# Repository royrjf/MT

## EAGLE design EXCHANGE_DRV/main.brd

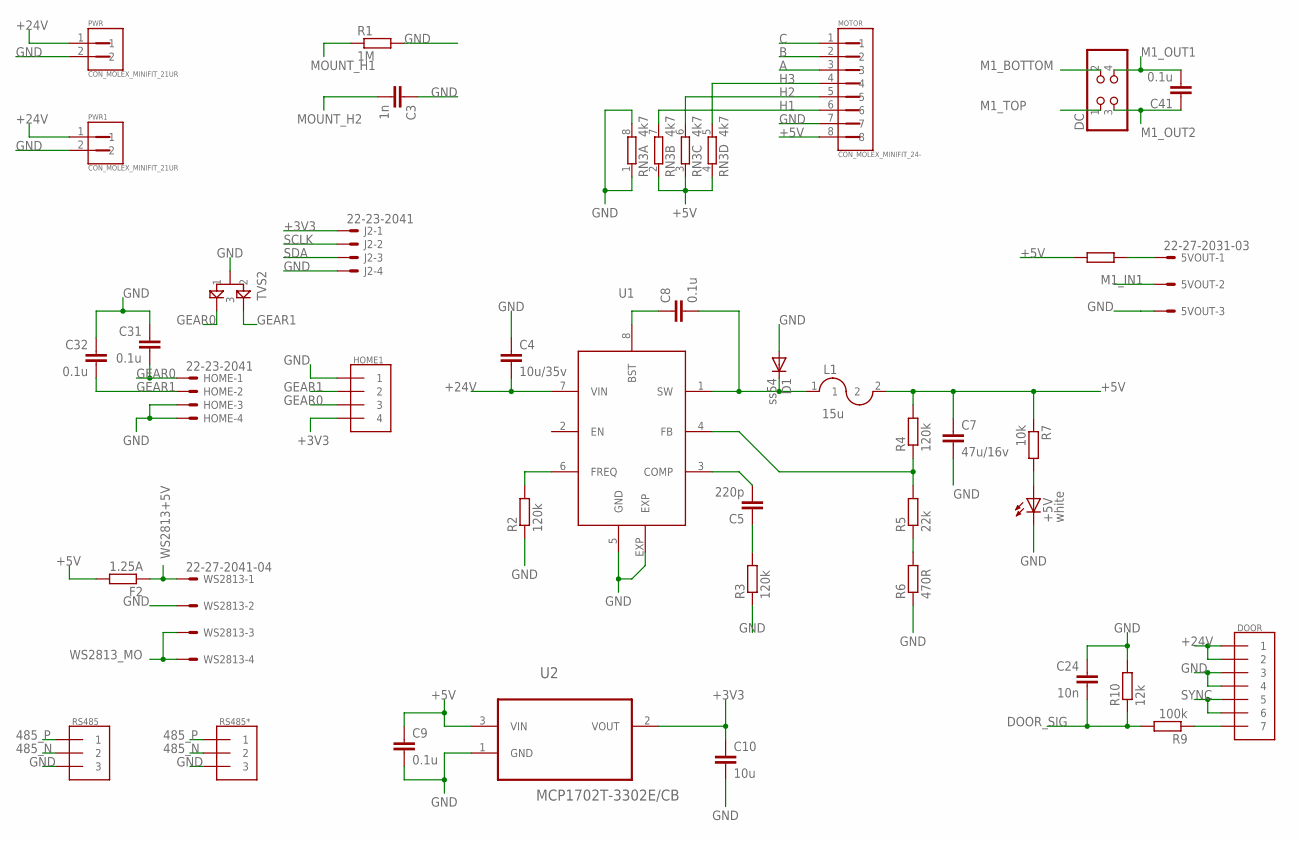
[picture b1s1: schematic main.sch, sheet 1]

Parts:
5VOUT: 22-27-2031-03; 6410-03
+5V: white; SML0603
C3: 1n; C0603
C4: 10u/35v; C1206
C5: 220p; C0603
C7: 47u/16v; C1206
C8, C9, C31, C32, C41: 0.1u; C0603
C10: 10u; C0603
C24: 10n; C0603
D1: ss54; DO214BA
DC: 430450414; 4304504-TH
DOOR: 1LINE_SOCKET_2MM_7
F1, F2: 1.25A; R1206
HOME: 22-23-2041
HOME1: 1LINE_SOCKET_2MM_4_90
J2: 22-23-2041
L1: 15u; RCL_L_CDRH8D38
MOTOR: CON_MOLEX_MINIFIT_24-; CON_MOLEX_MINIFIT_2*4
PWR, PWR1: CON_MOLEX_MINIFIT_21UR; CON_MOLEX_MINIFIT_2*1_UR
R1: 1M; R0603
R2, R3, R4: 120k; R0603
R5: 22k; R0603
R6: 470R; R0603
R7: 10k; R0603
R9: 100k; R0603
R10: 12k; R0603
RN3: 4k7; EXB38V
RS485, RS485*: 1LINE_SOCKET_2MM_3_90
TVS2: PESD33; RCL_SOT23
U1: MP2560; SOIC-8E
U2: MCP1702T-3302E/CB; SOT95P255X145-3N
WS2813: 22-27-2041-04; 6410-04

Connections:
485_N: RS485.P$2 (2), RS485*.P$2 (2); also elsewhere on the board
485_P: RS485.P$1 (1), RS485*.P$1 (1); also elsewhere on the board
+3V3: C10.1, HOME1.P$4 (4), J2.1, U2.2 (VOUT); also elsewhere on the board
+5V: C7.1, C9.1, F1.2, F2.2, L1.2, MOTOR.8, R4.2, R7.1, RN3.2 (1), RN3.3 (1), RN3.4 (1), U2.3 (VIN)
+24V: C4.2, DOOR.P$1 (1), DOOR.P$2 (2), PWR.1, PWR1.1, U1.7 (VIN); also elsewhere on the board
A: MOTOR.3; also elsewhere on the board
B: MOTOR.2; also elsewhere on the board
C: MOTOR.1; also elsewhere on the board
DOOR_SIG: C24.2, R9.2, R10.1; also elsewhere on the board
GEAR0: C31.2, HOME.1, HOME1.P$3 (3), TVS2.1; also elsewhere on the board
GEAR1: C32.2, HOME.2, HOME1.P$2 (2), TVS2.2; also elsewhere on the board
GND: 5VOUT.3, +5V.C, C3.1, C4.1, C7.2, C9.2, C10.2, C24.1, C31.1, C32.1, D1.A, DOOR.P$3 (3), DOOR.P$4 (4), HOME.3, HOME.4, HOME1.P$1 (1), J2.4, MOTOR.7, PWR.2, PWR1.2, R1.2, R2.1, R3.1, R6.1, R10.2, RN3.1, RN3.8 (2), RS485.P$3 (3), RS485*.P$3 (3), TVS2.3, U1.5 (GND), U1.EXP, U2.1 (GND), WS2813.2; also elsewhere on the board
H1: MOTOR.6, RN3.7 (2); also elsewhere on the board
H2: MOTOR.5, RN3.6 (2); also elsewhere on the board
H3: MOTOR.4, RN3.5 (2); also elsewhere on the board
M1_BOTTOM: DC.2
M1_IN1: 5VOUT.2; also elsewhere on the board
M1_OUT1: C41.2, DC.4; also elsewhere on the board
M1_OUT2: C41.1, DC.3; also elsewhere on the board
M1_TOP: DC.1
MOUNT_H1: R1.1
MOUNT_H2: C3.2
unnamed: C8.2, D1.C, L1.1, U1.1 (SW)
unnamed: 5VOUT.1, F1.1
unnamed: C5.1, R3.2
unnamed: R2.2, U1.6 (FREQ)
unnamed: C5.2, U1.3 (COMP)
unnamed: R5.1, R6.2
unnamed: R4.1, R5.2, U1.4 (FB)
unnamed: C8.1, U1.8 (BST)
unnamed: +5V.A, R7.2
SCLK: J2.2; also elsewhere on the board
SDA: J2.3; also elsewhere on the board
SIG-DOOR: DOOR.P$7 (7), R9.1
SYNC: DOOR.P$5 (5), DOOR.P$6 (6)
WS2813+5V: F2.1, WS2813.1; also elsewhere on the board
WS2813_MO: WS2813.3, WS2813.4; also elsewhere on the board

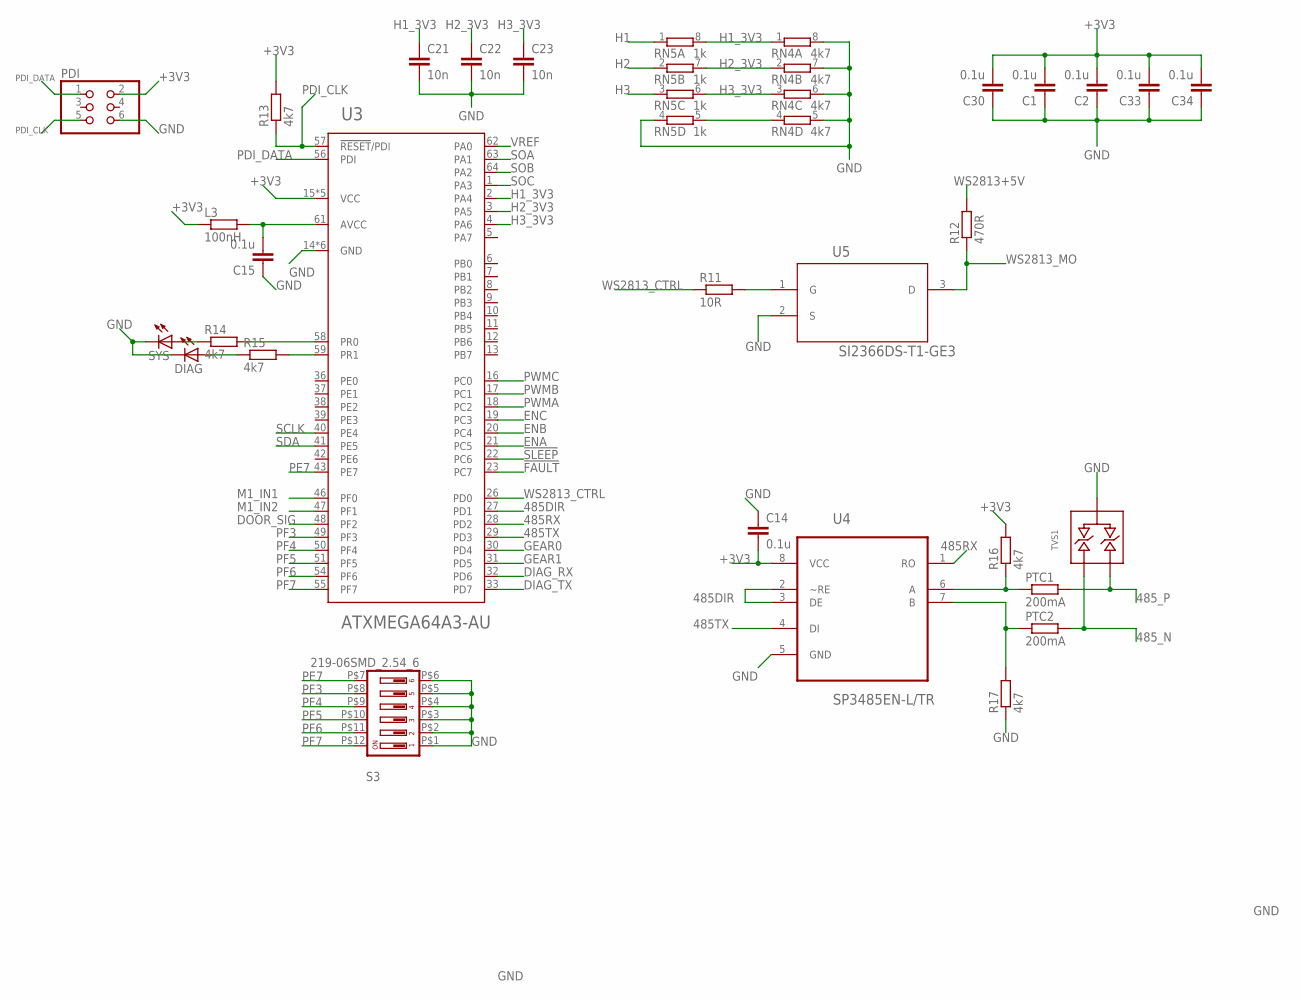
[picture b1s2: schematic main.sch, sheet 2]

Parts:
C1, C2, C14, C15, C30, C33, C34: 0.1u; C0603
C21, C22, C23: 10n; C0603
DIAG: LEDSML0603; SML0603
L3: 100nH; R0603
PDI: PINHD-2X3; 2X03
PTC1, PTC2: 200mA; R0805
R11: 10R; R0603
R12: 470R; R0603
R13, R14, R15, R16, R17: 4k7; R0603
RN4: 4k7; EXB38V
RN5: 1k; EXB38V
S3: 219-06SMD_2.54_6; SMD-2.54-6
SYS: LEDSML0603; SML0603
TVS1: SM712; SOT23
U3: ATXMEGA64A3-AU; TQFP-64A-64
U4: SP3485EN-L/TR; SOIC127P600X175-8N
U5: SI2366DS-T1-GE3; SOT95P237X112-3N

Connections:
485DIR: U3.27 (PD1), U4.2 (~RE), U4.3 (DE)
485RX: U3.28 (PD2), U4.1 (RO)
485TX: U3.29 (PD3), U4.4 (DI)
485_N: PTC2.2, TVS1.P$1; also elsewhere on the board
485_P: PTC1.2, TVS1.P$2; also elsewhere on the board
!FAULT: U3.23 (PC7); also elsewhere on the board
!SLEEP: U3.22 (PC6); also elsewhere on the board
+3V3: C1.2, C2.2, C14.2, C30.2, C33.2, C34.2, L3.1, PDI.2, R13.2, R16.2, U3.15 (VCC), U3.25 (VCC), U3.35 (VCC), U3.45 (VCC), U3.53 (VCC), U4.8 (VCC); also elsewhere on the board
DIAG_RX: U3.32 (PD6)
DIAG_TX: U3.33 (PD7)
DOOR_SIG: U3.48 (PF2); also elsewhere on the board
ENA: U3.21 (PC5); also elsewhere on the board
ENB: U3.20 (PC4); also elsewhere on the board
ENC: U3.19 (PC3); also elsewhere on the board
GEAR0: U3.30 (PD4); also elsewhere on the board
GEAR1: U3.31 (PD5); also elsewhere on the board
GND: C1.1, C2.1, C14.1, C15.1, C21.2, C22.2, C23.2, C30.1, C33.1, C34.1, DIAG.C, PDI.6, R17.1, RN4.4 (1), RN4.5 (2), RN4.6 (2), RN4.7 (2), RN4.8 (2), RN5.4 (1), RN5.5 (2), S3.P$1 (1), S3.P$2 (2), S3.P$3 (3), S3.P$4 (4), S3.P$5 (5), S3.P$6 (6), SYS.C, TVS1.P$3, U3.14 (GND), U3.24 (GND), U3.34 (GND), U3.44 (GND), U3.52 (GND), U3.60 (GND), U4.5 (GND), U5.2 (S); also elsewhere on the board
H1: RN5.1; also elsewhere on the board
H1_3V3: C21.1, RN4.1, RN5.8 (2), U3.2 (PA4)
H2: RN5.2 (1); also elsewhere on the board
H2_3V3: C22.1, RN4.2 (1), RN5.7 (2), U3.3 (PA5)
H3: RN5.3 (1); also elsewhere on the board
H3_3V3: C23.1, RN4.3 (1), RN5.6 (2), U3.4 (PA6)
M1_IN1: U3.46 (PF0); also elsewhere on the board
M1_IN2: U3.47 (PF1); also elsewhere on the board
unnamed: PTC2.1, R17.2, U4.7 (B)
unnamed: PTC1.1, R16.1, U4.6 (A)
unnamed: C15.2, L3.2, U3.61 (AVCC)
unnamed: R14.2, U3.58 (PR0)
unnamed: R14.1, SYS.A
unnamed: R15.2, U3.59 (PR1)
unnamed: DIAG.A, R15.1
unnamed: R11.2, U5.1 (G)
PDI_CLK: PDI.5, R13.1, U3.57 (!RESET!/PDI)
PDI_DATA: PDI.1, U3.56 (PDI)
PE7: S3.P$7 (7), U3.43 (PE7)
PF3: S3.P$8 (8), U3.49 (PF3)
PF4: S3.P$9 (9), U3.50 (PF4)
PF5: S3.P$10 (10), U3.51 (PF5)
PF6: S3.P$11 (11), U3.54 (PF6)
PF7: S3.P$12 (12), U3.55 (PF7)
PWMA: U3.18 (PC2); also elsewhere on the board
PWMB: U3.17 (PC1); also elsewhere on the board
PWMC: U3.16 (PC0); also elsewhere on the board
SCLK: U3.40 (PE4); also elsewhere on the board
SDA: U3.41 (PE5); also elsewhere on the board
SOA: U3.63 (PA1); also elsewhere on the board
SOB: U3.64 (PA2); also elsewhere on the board
SOC: U3.1 (PA3); also elsewhere on the board
VREF: U3.62 (PA0); also elsewhere on the board
WS2813+5V: R12.2; also elsewhere on the board
WS2813_CTRL: R11.1, U3.26 (PD0)
WS2813_MO: R12.1, U5.3 (D); also elsewhere on the board

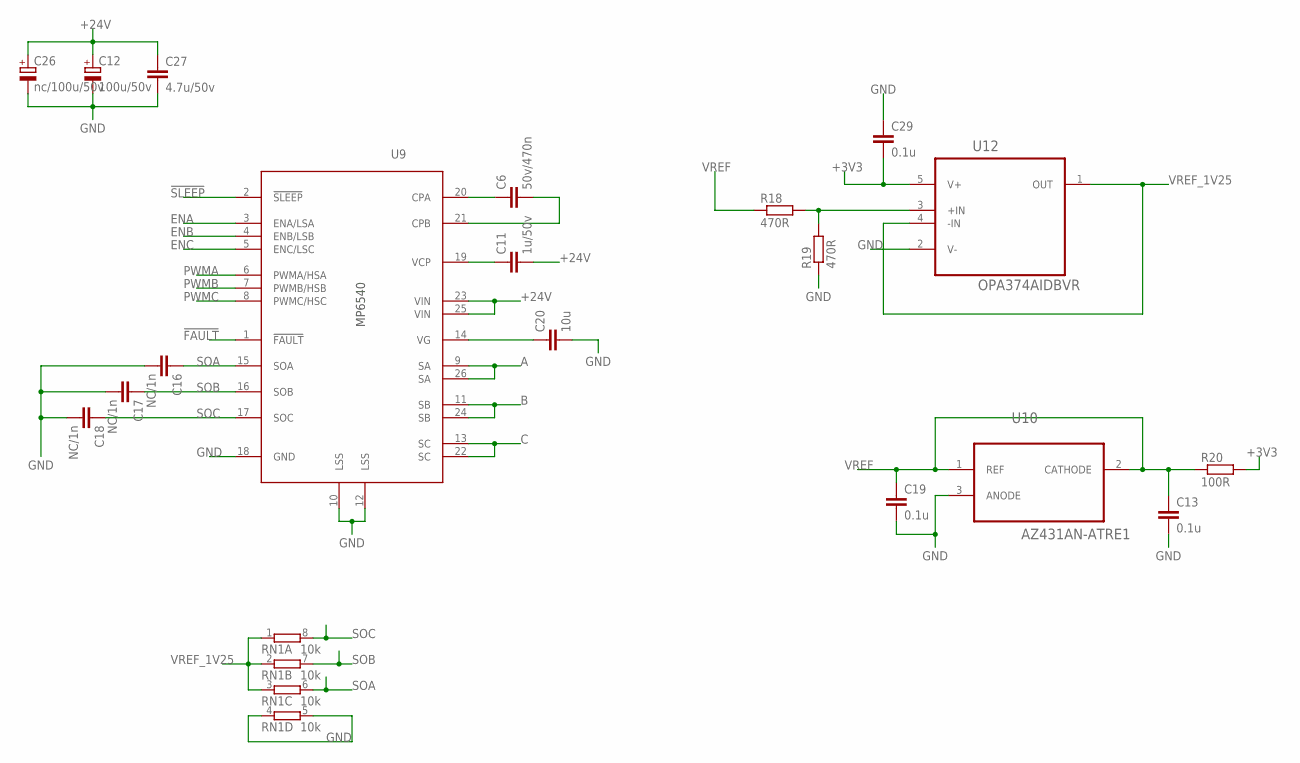
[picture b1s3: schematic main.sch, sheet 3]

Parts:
C6: 50v/470n; C0603
C11: 1u/50v; C0805
C12: 100u/50v; 140CLH-0810
C13, C19, C29: 0.1u; C0603
C16, C17, C18: NC/1n; C0603
C20: 10u; C0603
C26: nc/100u/50v; 140CLH-0810
C27: 4.7u/50v; C0805
R18, R19: 470R; R0603
R20: 100R; R0603
RN1: 10k; EXB38V
U9: MP6540; QFN-26
U10: AZ431AN-ATRE1; SOT95P237X112-3N
U12: OPA374AIDBVR; SOT95P280X145-5N

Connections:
!FAULT: U9.1 (!FAULT); also elsewhere on the board
!SLEEP: U9.2 (!SLEEP); also elsewhere on the board
+3V3: C29.2, R20.2, U12.5 (V+); also elsewhere on the board
+24V: C11.2, C12.+, C26.+, C27.1, U9.23 (VIN), U9.25 (VIN); also elsewhere on the board
A: U9.9 (SA), U9.26 (SA); also elsewhere on the board
B: U9.11 (SB), U9.24 (SB); also elsewhere on the board
C: U9.13 (SC), U9.22 (SC); also elsewhere on the board
ENA: U9.3 (ENA/LSA); also elsewhere on the board
ENB: U9.4 (ENB/LSB); also elsewhere on the board
ENC: U9.5 (ENC/LSC); also elsewhere on the board
GND: C12.-, C13.2, C16.2, C17.2, C18.2, C19.2, C20.2, C26.-, C27.2, C29.1, R19.1, RN1.4 (1), RN1.5 (2), U9.10 (LSS), U9.12 (LSS), U9.18 (GND), U10.3 (ANODE), U12.2 (V-); also elsewhere on the board
unnamed: R18.2, R19.2, U12.3 (+IN)
unnamed: C6.1, U9.20 (CPA)
unnamed: C6.2, U9.21 (CPB)
unnamed: C11.1, U9.19 (VCP)
unnamed: C20.1, U9.14 (VG)
PWMA: U9.6 (PWMA/HSA); also elsewhere on the board
PWMB: U9.7 (PWMB/HSB); also elsewhere on the board
PWMC: U9.8 (PWMC/HSC); also elsewhere on the board
SOA: C16.1, RN1.6 (2), U9.15 (SOA); also elsewhere on the board
SOB: C17.1, RN1.7 (2), U9.16 (SOB); also elsewhere on the board
SOC: C18.1, RN1.8 (2), U9.17 (SOC); also elsewhere on the board
VREF: C13.1, C19.1, R18.1, R20.1, U10.1 (REF), U10.2 (CATHODE); also elsewhere on the board
VREF_1V25: RN1.1, RN1.2 (1), RN1.3 (1), U12.1 (OUT), U12.4 (-IN)

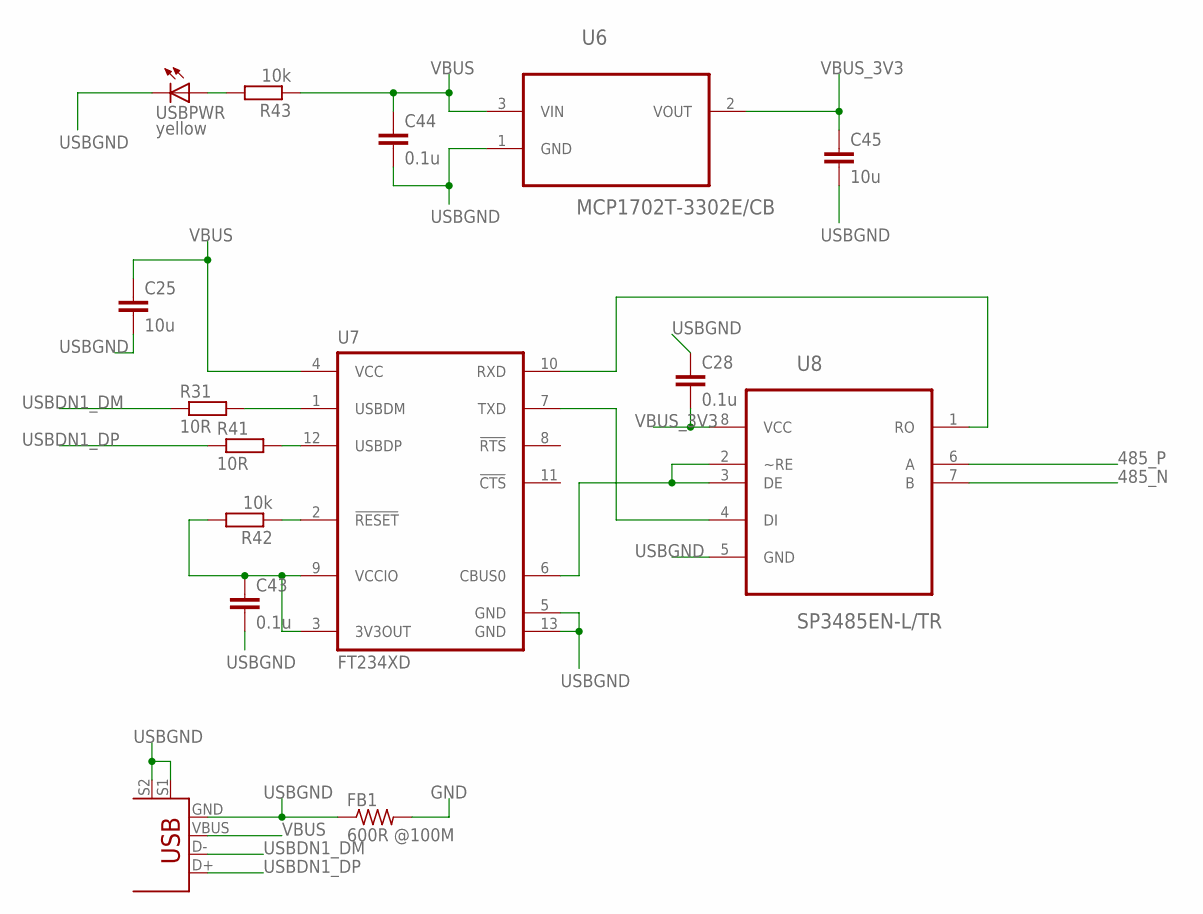
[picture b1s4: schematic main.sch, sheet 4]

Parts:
C25, C45: 10u; C0603
C28, C43, C44: 0.1u; C0603
FB1: 600R @100M; R0805
R31, R41: 10R; R0603
R42, R43: 10k; R0603
U6: MCP1702T-3302E/CB; SOT95P255X145-3N
U7: FT234XD; DFN12
U8: SP3485EN-L/TR; SOIC127P600X175-8N
USBPWR: yellow; SML0603
USBUP: USB+SHIELD; USB-B-PTH

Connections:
485_N: U8.7 (B); also elsewhere on the board
485_P: U8.6 (A); also elsewhere on the board
GND: FB1.2; also elsewhere on the board
unnamed: R31.2, U7.1 (USBDM)
unnamed: R41.2, U7.12 (USBDP)
unnamed: C43.1, R42.2, U7.3 (3V3OUT), U7.9 (VCCIO)
unnamed: R42.1, U7.2 (!RESET!)
unnamed: U7.7 (TXD), U8.4 (DI)
unnamed: U7.10 (RXD), U8.1 (RO)
unnamed: U7.6 (CBUS0), U8.2 (~RE), U8.3 (DE)
unnamed: R43.2, USBPWR.A
USBDN1_DM: R31.1, USBUP.D-
USBDN1_DP: R41.1, USBUP.D+
USBGND: C25.2, C28.1, C43.2, C44.2, C45.2, FB1.1, U6.1 (GND), U7.5 (GND), U7.13 (GND), U8.5 (GND), USBPWR.C, USBUP.GND, USBUP.S1, USBUP.S2
VBUS: C25.1, C44.1, R43.1, U6.3 (VIN), U7.4 (VCC), USBUP.VBUS
VBUS_3V3: C28.2, C45.1, U6.2 (VOUT), U8.8 (VCC)

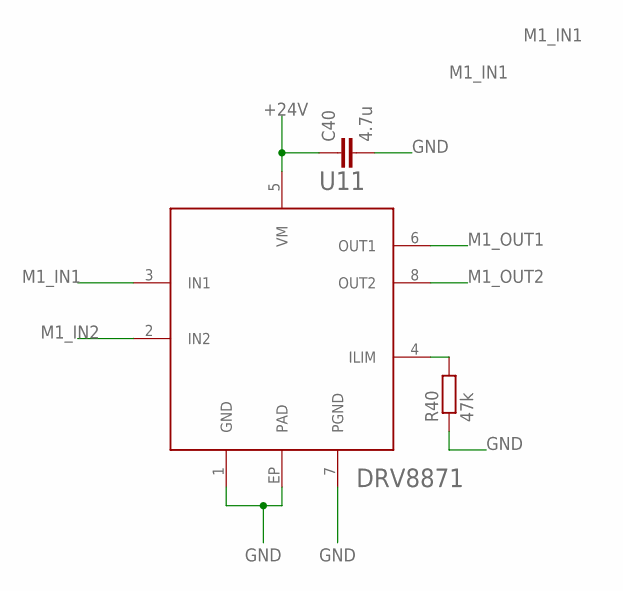
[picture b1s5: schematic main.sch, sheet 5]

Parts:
C40: 4.7u; C0805
R40: 47k; R0603
U11: DRV8871; 8HSOIC

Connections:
+24V: C40.1, U11.5 (VM); also elsewhere on the board
GND: C40.2, R40.1, U11.1 (GND), U11.7 (PGND), U11.EP (PAD); also elsewhere on the board
M1_IN1: U11.3 (IN1); also elsewhere on the board
M1_IN2: U11.2 (IN2); also elsewhere on the board
M1_OUT1: U11.6 (OUT1); also elsewhere on the board
M1_OUT2: U11.8 (OUT2); also elsewhere on the board
unnamed: R40.2, U11.4 (ILIM)

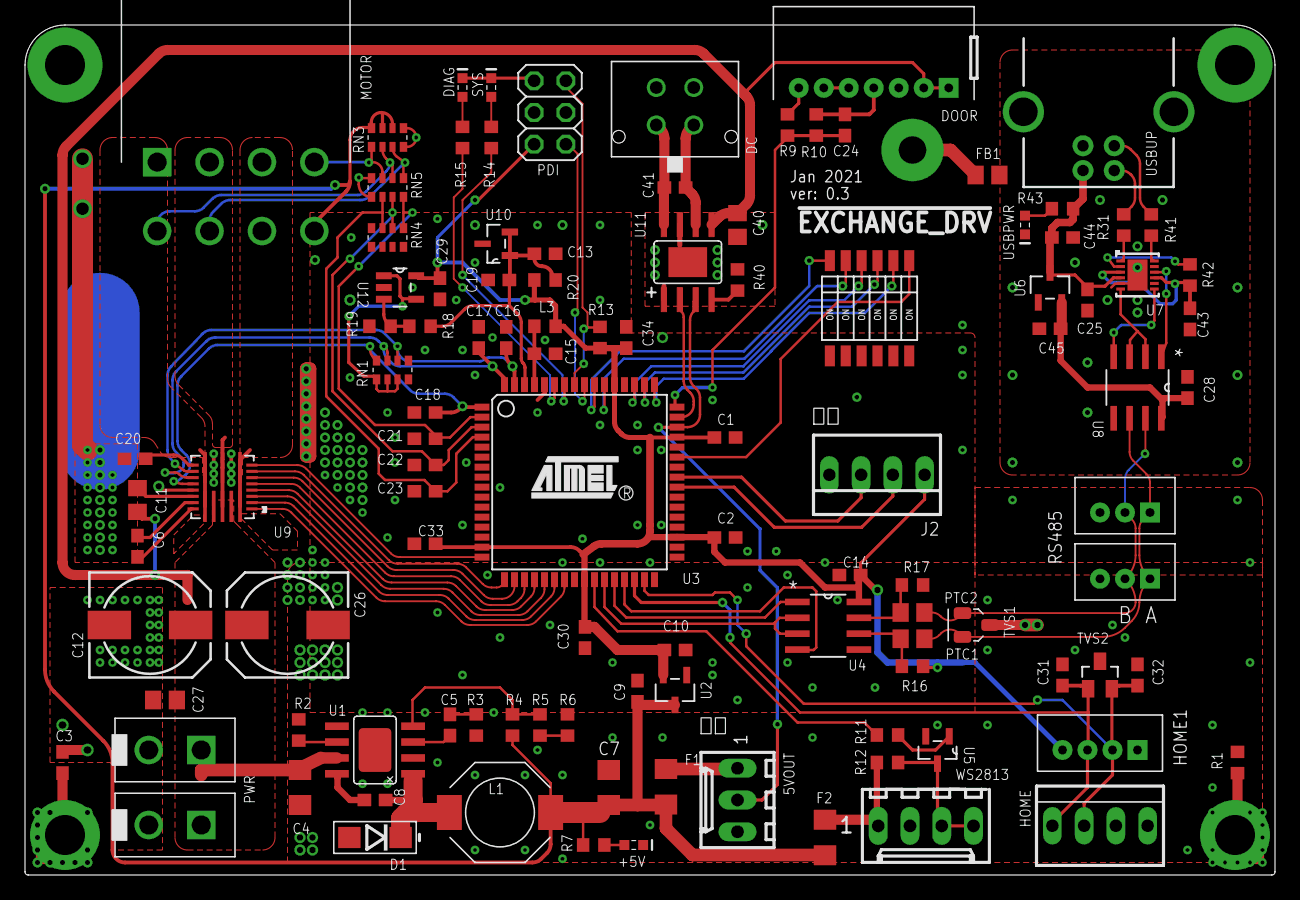
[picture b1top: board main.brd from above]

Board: 2 copper layers, 100.0 x 68.0 mm, 108 parts (0 on the bottom side), 89 nets.

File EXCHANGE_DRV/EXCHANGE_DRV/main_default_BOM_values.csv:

Qty,Comment,Device,Designator,Footprint,Description,,,,,
2,1LINE_SOCKET_2MM_3_90,1LINE_SOCKET_2MM_3_90,"RS485, RS485*",1LINE_SOCKET_2MM_3_90,,,,,,
1,1LINE_SOCKET_2MM_4_90,1LINE_SOCKET_2MM_4_90,HOME1,1LINE_SOCKET_2MM_4_90,,,,,,
1,1LINE_SOCKET_2MM_7,1LINE_SOCKET_2MM_7,DOOR,1LINE_SOCKET_2MM_7,,,,,,
1,219-06SMD_2.54_6,219-06SMD_2.54_6,S3,SMD-2.54-6,Surface Mount DIP Switch Series 219 SMT,,,,,
1,22-23-2041,22-23-2041,J2,22-23-2041,.100 (2.54mm) Center Header - 4 Pin",,,,,
1,22-23-2041,22-23-2041,HOME,22-23-2041,.100 (2.54mm) Center Header - 4 Pin",,,,,
1,22-27-2031-03,22-27-2031-03,5VOUT,Mar-10,CONNECTOR,,,,,
1,22-27-2041-04,22-27-2041-04,WS2813,Apr-10,CONNECTOR,,,,,
1,,430450414,DC,4304504-TH,4-pin Male Molex Connector,,,,,
1,10k,4R-NEXB38V,RN1,EXB38V,Array Chip Resistor,,,,,
1,1k,4R-NEXB38V,RN5,EXB38V,Array Chip Resistor,,,,,
2,4k7,4R-NEXB38V,"RN3, RN4",EXB38V,Array Chip Resistor,,,,,
1,ATXMEGA64A3-AU,ATXMEGA64A3-AU,U3,TQFP-64A-64,8/16-bit XMEGA A3 Microcontroller,,,,,
18,0.1u,C-EUC0603,"C1, C2, C8, C9, C13, C14, C15, C19, C28, C29, C30, C31, C32, C33, C34, C41, C43, C44",C0603,"CAPACITOR, European symbol",,,,,
4,10n,C-EUC0603,"C21, C22, C23, C24",C0603,"CAPACITOR, European symbol",,,,,
4,10u,C-EUC0603,"C10, C20, C25, C45",C0603,"CAPACITOR, European symbol",,,,,
1,1n,C-EUC0603,C3,C0603,"CAPACITOR, European symbol",,,,,
1,220p,C-EUC0603,C5,C0603,"CAPACITOR, European symbol",,,,,
1,50v/470n,C-EUC0603,C6,C0603,"CAPACITOR, European symbol",,,,,
3,NC/1n,C-EUC0603,"C16, C17, C18",C0603,"CAPACITOR, European symbol",,,,,
1,1u/50v,C-EUC0805,C11,C0805,"CAPACITOR, European symbol",,,,,
1,4.7u,C-EUC0805,C40,C0805,"CAPACITOR, European symbol",,,,,
1,4.7u/50v,C-EUC0805,C27,C0805,"CAPACITOR, European symbol",,,,,
1,10u/35v,C-EUC1206,C4,C1206,"CAPACITOR, European symbol",,,,,
1,47u/16v,C-EUC1206,C7,C1206,"CAPACITOR, European symbol",,,,,
2,CON_MOLEX_MINIFIT_21UR,CON_MOLEX_MINIFIT_21UR,"PWR, PWR1",CON_MOLEX_MINIFIT_2*1_UR,,,,,,
1,CON_MOLEX_MINIFIT_24-,CON_MOLEX_MINIFIT_24-,MOTOR,CON_MOLEX_MINIFIT_2*4,,,,,,
1,100u/50v,CPOL-EU140CLH-0810,C12,140CLH-0810,"POLARIZED CAPACITOR, European symbol",,,,,
1,nc/100u/50v,CPOL-EU140CLH-0810,C26,140CLH-0810,"POLARIZED CAPACITOR, European symbol",,,,,
1,ss54,DIODE-DO214BA,D1,DO214BA,DIODE,,,,,
1,DRV8871,DRV8871,U11,8HSOIC,,,,,,
1,FT234XD,FT234XD,U7,DFN12,USB TO BASIC UART IC,,,,,
1,PESD33,GSOT05C-GS08,TVS2,RCL_SOT23,,,,,,
2,,LEDSML0603,"DIAG, SYS",SML0603,LED,,,,,
1,white,LEDSML0603,+5V,SML0603,LED,,,,,
1,yellow,LEDSML0603,USBPWR,SML0603,LED,,,,,
2,SP3485EN-L/TR,MAX3485CSA+,"U4, U8",SOIC127P600X175-8N,"3.3V-Powered, 10Mbps and Slew-Rate-Limited True RS-485/RS-422 Transceivers",,,,,SOIC-8
2,MCP1702T-3302E/CB,MCP1702T-3302E/CB,"U2, U6",SOT95P255X145-3N,250 mA Low Quiescent Current LDO Regulator,,,,,SOT23-3
1,MP2560,MP2560,U1,SOIC-8E,,,,,,
1,MP6540,MP6540,U9,QFN-26,,,,,,
1,OPA374AIDBVR,OPA378AIDBVT,U12,SOT95P280X145-5N,"Low-Noise, 900kHz, RRIO Precision OPERATIONAL AMPLIFIER Zerø-Drift Series",,,,,SOT-23-5
1,,PINHD-2X3,PDI,2X03,PIN HEADER,,,,,
1,100R,R-EU_R0603,R20,R0603,"RESISTOR, European symbol",,,,,
1,100k,R-EU_R0603,R9,R0603,"RESISTOR, European symbol",,,,,
1,100nH,R-EU_R0603,L3,R0603,"RESISTOR, European symbol",,,,,
3,10R,R-EU_R0603,"R11, R31, R41",R0603,"RESISTOR, European symbol",,,,,
3,10k,R-EU_R0603,"R7, R42, R43",R0603,"RESISTOR, European symbol",,,,,
3,120k,R-EU_R0603,"R2, R3, R4",R0603,"RESISTOR, European symbol",,,,,
1,12k,R-EU_R0603,R10,R0603,"RESISTOR, European symbol",,,,,
1,1M,R-EU_R0603,R1,R0603,"RESISTOR, European symbol",,,,,
1,22k,R-EU_R0603,R5,R0603,"RESISTOR, European symbol",,,,,
4,470R,R-EU_R0603,"R6, R12, R18, R19",R0603,"RESISTOR, European symbol",,,,,
1,47k,R-EU_R0603,R40,R0603,"RESISTOR, European symbol",,,,,
5,4k7,R-EU_R0603,"R13, R14, R15, R16, R17",R0603,"RESISTOR, European symbol",,,,,
2,200mA,R-EU_R0805,"PTC1, PTC2",R0805,"RESISTOR, European symbol",,,,,
2,1.25A,R-EU_R1206,"F1, F2",R1206,"RESISTOR, European symbol",,,,,
1,600R @100M,R-US_R0805,FB1,R0805,"RESISTOR, American symbol",,,,,
1,15u,RCL_L_CDRH8D38,L1,RCL_L_CDRH8D38,http://products.sumida.com/products/pdf/CDRH8D38.pdf,,,,,
1,SI2366DS-T1-GE3,SI2366DS-T1-GE3,U5,SOT95P237X112-3N,N-Channel 30 V (D-S) MOSFET,,,,,SOT-23-3
1,SM712,SM712,TVS1,SOT23,,,,,,
1,AZ431AN-ATRE1,TL431BQDBZR,U10,SOT95P237X112-3N,PRECISION PROGRAMMABLE REFERENCE,,,,,SOT23-3
1,USB+SHIELD,USB+SHIELD,USBUP,USB-B-PTH,USB+Shield,,,,,

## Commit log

2021-09-20 exchange drv
2021-09-20 v3.0

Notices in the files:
parts and their libraries:
SparkFun-Connectors: Licensing: Creative Commons ShareAlike 4.0 International - https://creativecommons.org/licenses/by-sa/4.0
